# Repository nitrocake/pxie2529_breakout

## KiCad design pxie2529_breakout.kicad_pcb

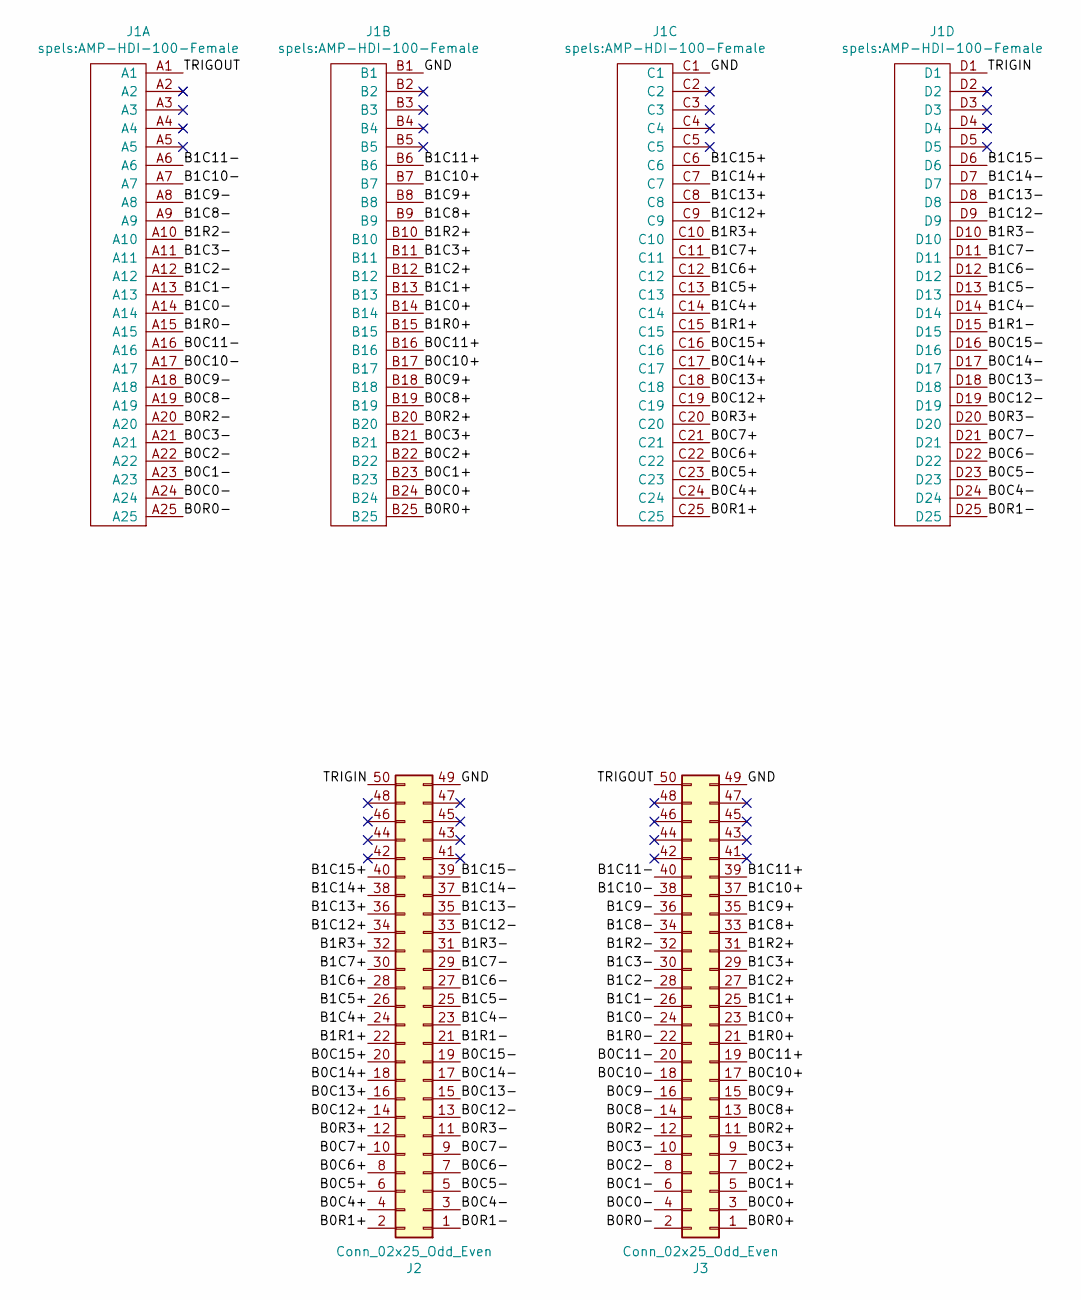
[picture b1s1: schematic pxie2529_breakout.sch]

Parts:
J1: connector-25x4; AMP-HDI-100-Female
J2, J3: Conn_02x25_Odd_Even; IDC-Header_2x25_P2.54mm_Latch12.0mm_Vertical

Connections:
/B0C0+: J1.B24, J3.3
/B0C0-: J1.A24, J3.4
/B0C1+: J1.B23, J3.5
/B0C1-: J1.A23, J3.6
/B0C2+: J1.B22, J3.7
/B0C2-: J1.A22, J3.8
/B0C3+: J1.B21, J3.9
/B0C3-: J1.A21, J3.10
/B0C4+: J1.C24, J2.4
/B0C4-: J1.D24, J2.3
/B0C5+: J1.C23, J2.6
/B0C5-: J1.D23, J2.5
/B0C6+: J1.C22, J2.8
/B0C6-: J1.D22, J2.7
/B0C7+: J1.C21, J2.10
/B0C7-: J1.D21, J2.9
/B0C8+: J1.B19, J3.13
/B0C8-: J1.A19, J3.14
/B0C9+: J1.B18, J3.15
/B0C9-: J1.A18, J3.16
/B0C10+: J1.B17, J3.17
/B0C10-: J1.A17, J3.18
/B0C11+: J1.B16, J3.19
/B0C11-: J1.A16, J3.20
/B0C12+: J1.C19, J2.14
/B0C12-: J1.D19, J2.13
/B0C13+: J1.C18, J2.16
/B0C13-: J1.D18, J2.15
/B0C14+: J1.C17, J2.18
/B0C14-: J1.D17, J2.17
/B0C15+: J1.C16, J2.20
/B0C15-: J1.D16, J2.19
/B0R0+: J1.B25, J3.1
/B0R0-: J1.A25, J3.2
/B0R1+: J1.C25, J2.2
/B0R1-: J1.D25, J2.1
/B0R2+: J1.B20, J3.11
/B0R2-: J1.A20, J3.12
/B0R3+: J1.C20, J2.12
/B0R3-: J1.D20, J2.11
/B1C0+: J1.B14, J3.23
/B1C0-: J1.A14, J3.24
/B1C1+: J1.B13, J3.25
/B1C1-: J1.A13, J3.26
/B1C2+: J1.B12, J3.27
/B1C2-: J1.A12, J3.28
/B1C3+: J1.B11, J3.29
/B1C3-: J1.A11, J3.30
/B1C4+: J1.C14, J2.24
/B1C4-: J1.D14, J2.23
/B1C5+: J1.C13, J2.26
/B1C5-: J1.D13, J2.25
/B1C6+: J1.C12, J2.28
/B1C6-: J1.D12, J2.27
/B1C7+: J1.C11, J2.30
/B1C7-: J1.D11, J2.29
/B1C8+: J1.B9, J3.33
/B1C8-: J1.A9, J3.34
/B1C9+: J1.B8, J3.35
/B1C9-: J1.A8, J3.36
/B1C10+: J1.B7, J3.37
/B1C10-: J1.A7, J3.38
/B1C11+: J1.B6, J3.39
/B1C11-: J1.A6, J3.40
/B1C12+: J1.C9, J2.34
/B1C12-: J1.D9, J2.33
/B1C13+: J1.C8, J2.36
/B1C13-: J1.D8, J2.35
/B1C14+: J1.C7, J2.38
/B1C14-: J1.D7, J2.37
/B1C15+: J1.C6, J2.40
/B1C15-: J1.D6, J2.39
/B1R0+: J1.B15, J3.21
/B1R0-: J1.A15, J3.22
/B1R1+: J1.C15, J2.22
/B1R1-: J1.D15, J2.21
/B1R2+: J1.B10, J3.31
/B1R2-: J1.A10, J3.32
/B1R3+: J1.C10, J2.32
/B1R3-: J1.D10, J2.31
/GND: J1.B1, J1.C1, J2.49, J3.49
/TRIGIN: J1.D1, J2.50
/TRIGOUT: J1.A1, J3.50

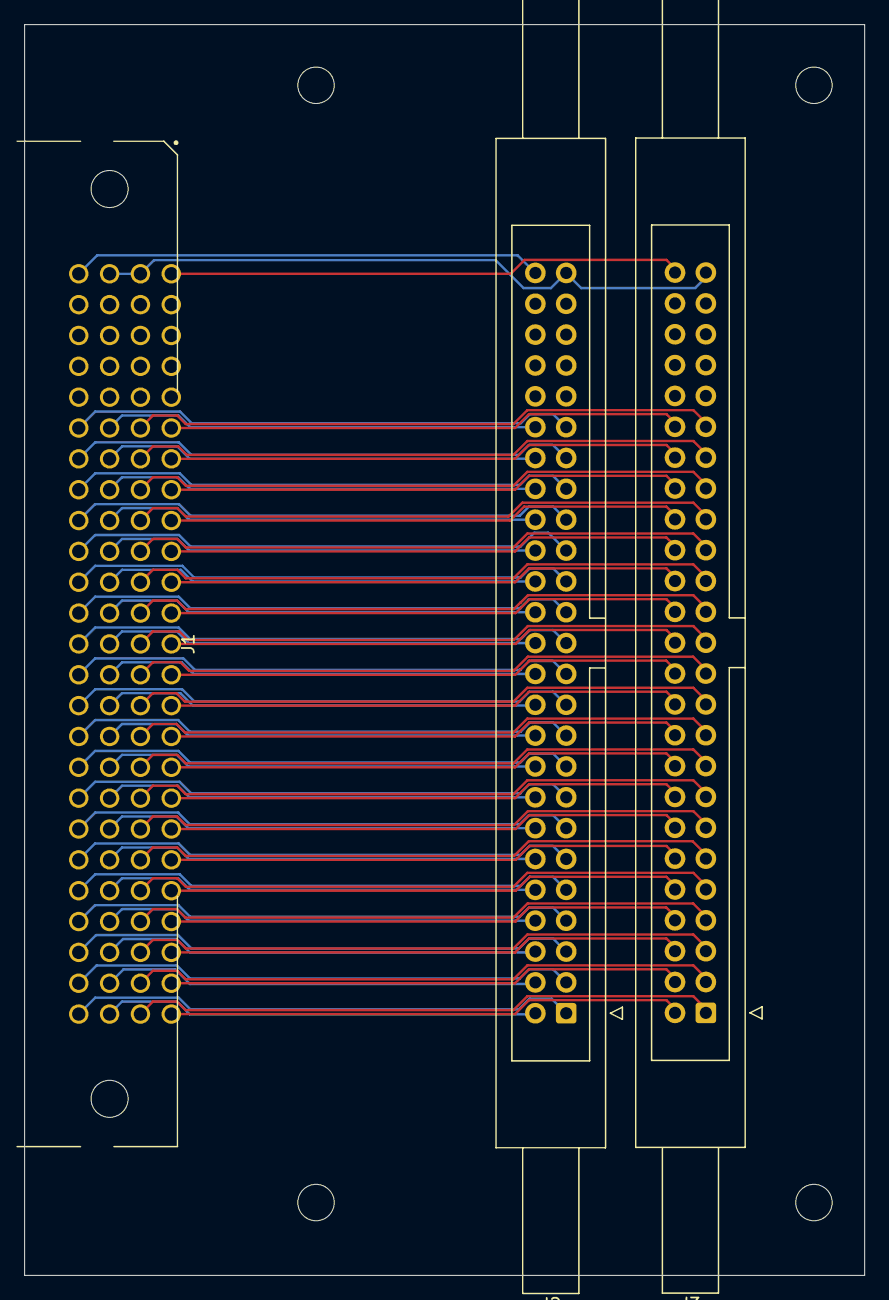
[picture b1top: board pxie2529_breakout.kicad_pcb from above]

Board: 2 copper layers, 69.2 x 103.0 mm, 3 parts (0 on the bottom side), 83 nets.

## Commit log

2022-04-12 finished routing
2022-04-13 ground connection added
2022-04-14 fixed connector orientation
